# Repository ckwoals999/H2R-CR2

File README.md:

# H2R-CR2
Robot-Arduino-Cleaning Robot

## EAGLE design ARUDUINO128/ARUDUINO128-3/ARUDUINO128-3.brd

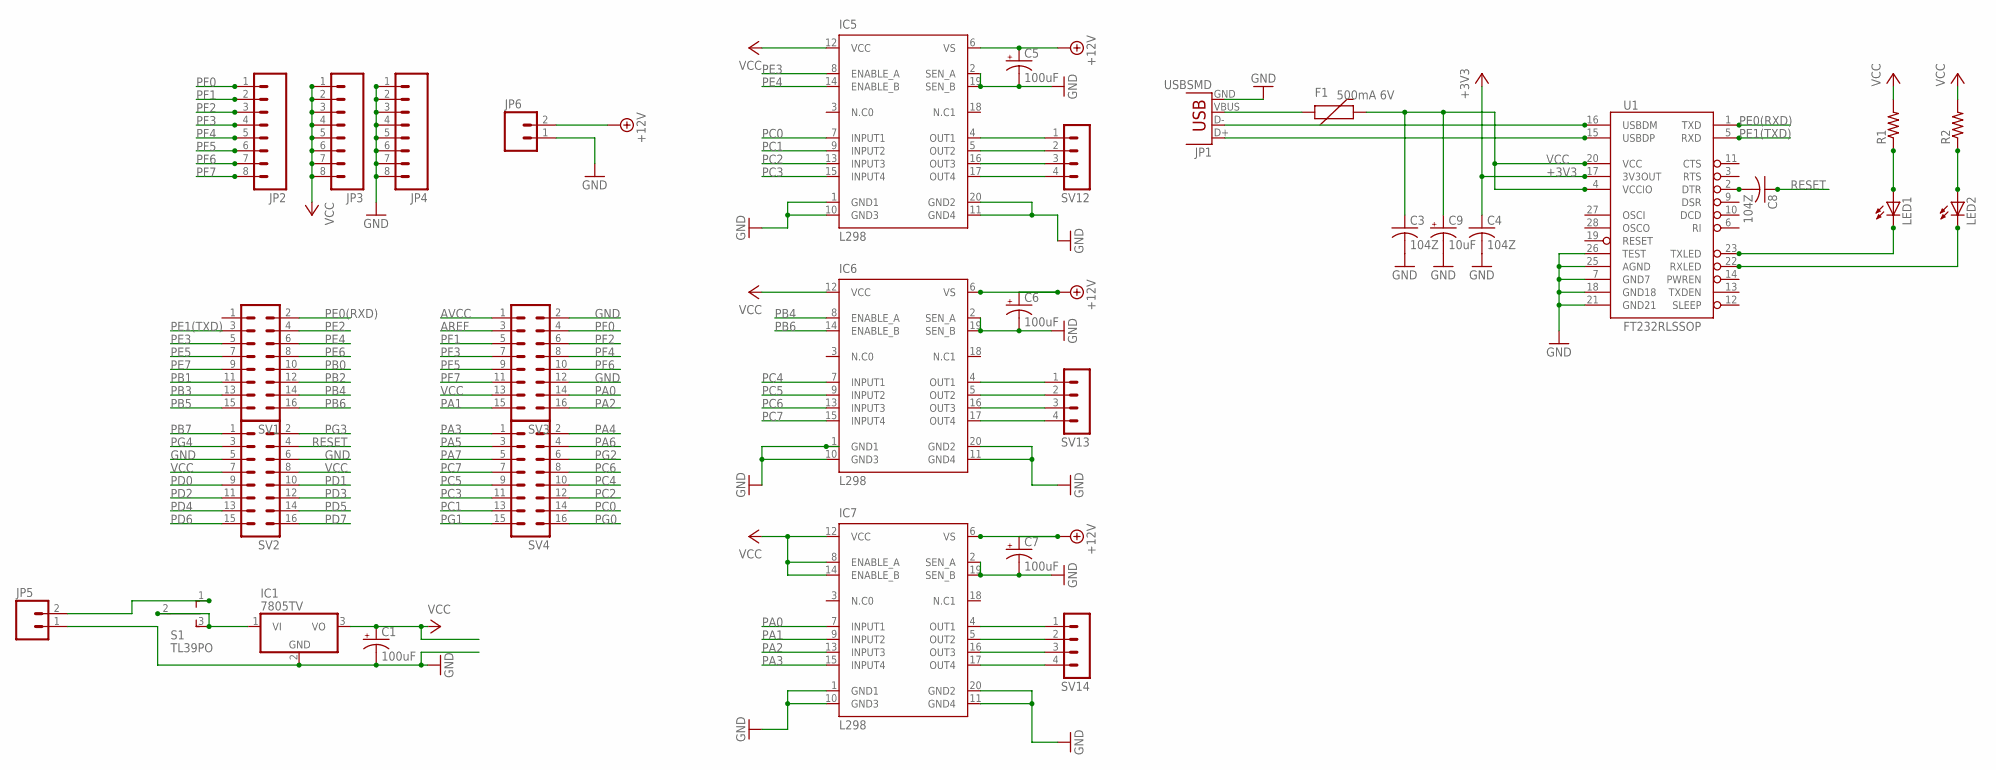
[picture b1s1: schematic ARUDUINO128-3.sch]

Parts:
C1, C5, C6, C7: 100uF; 153CLV-0807
C3, C4, C8: 104Z; C0603K
C9: 10uF; A/3216-18W
F1: 500mA 6V; PTC-1206
IC1: 7805TV; TO220V
IC5, IC6, IC7: L298; POWERSO-20
JP1: USBSMD; USB-MINIB
JP2, JP3, JP4: M08; 1X08_ROUND
JP5, JP6: M02PTH; 1X02
LED1, LED2: LEDCHIPLED_0603; CHIPLED_0603
R1, R2: R-US_M0805; M0805
S1: TL39PO; TL3XPO
SV1, SV2, SV3, SV4: MA08-2
SV12, SV13, SV14: MA04-1
U1: FT232RLSSOP; SSOP28DB

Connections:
+3V3: C4.1, U1.17 (3V3OUT)
+12V: C5.+, C6.+, C7.+, IC5.6 (VS), IC6.6 (VS), IC7.6 (VS), JP6.2
AREF: SV3.3
AVCC: SV3.1
GND: C1.-, C3.2, C4.2, C5.-, C6.-, C7.-, C9.-, IC1.2 (GND), IC5.1 (GND1), IC5.2 (SEN_A), IC5.10 (GND3), IC5.11 (GND4), IC5.19 (SEN_B), IC5.20 (GND2), IC6.1 (GND1), IC6.2 (SEN_A), IC6.10 (GND3), IC6.11 (GND4), IC6.19 (SEN_B), IC6.20 (GND2), IC7.1 (GND1), IC7.2 (SEN_A), IC7.10 (GND3), IC7.11 (GND4), IC7.19 (SEN_B), IC7.20 (GND2), JP1.GND, JP4.1, JP4.2, JP4.3, JP4.4, JP4.5, JP4.6, JP4.7, JP4.8, JP5.1, JP6.1, SV2.5, SV2.6, SV3.2, SV3.12, U1.7 (GND7), U1.18 (GND18), U1.21 (GND21), U1.25 (AGND), U1.26 (TEST)
unnamed: JP5.2, S1.1 (O)
unnamed: IC1.1 (VI), S1.2, S1.3 (S)
unnamed: F1.1, JP1.VBUS
unnamed: JP1.D-, U1.16 (USBDM)
unnamed: JP1.D+, U1.15 (USBDP)
unnamed: LED1.A, R1.1
unnamed: LED2.A, R2.1
unnamed: LED1.C, U1.23 (TXLED)
unnamed: LED2.C, U1.22 (RXLED)
unnamed: C8.2, U1.2 (DTR)
unnamed: IC5.4 (OUT1), SV12.1
unnamed: IC5.5 (OUT2), SV12.2
unnamed: IC5.16 (OUT3), SV12.3
unnamed: IC5.17 (OUT4), SV12.4
unnamed: IC6.4 (OUT1), SV13.1
unnamed: IC6.5 (OUT2), SV13.2
unnamed: IC6.16 (OUT3), SV13.3
unnamed: IC6.17 (OUT4), SV13.4
unnamed: IC7.4 (OUT1), SV14.1
unnamed: IC7.5 (OUT2), SV14.2
unnamed: IC7.16 (OUT3), SV14.3
unnamed: IC7.17 (OUT4), SV14.4
PA0: IC7.7 (INPUT1), SV3.14
PA1: IC7.9 (INPUT2), SV3.15
PA2: IC7.13 (INPUT3), SV3.16
PA3: IC7.15 (INPUT4), SV4.1
PA4: SV4.2
PA5: SV4.3
PA6: SV4.4
PA7: SV4.5
PB0: SV1.10
PB1: SV1.11
PB2: SV1.12
PB3: SV1.13
PB4: IC6.8 (ENABLE_A), SV1.14
PB5: SV1.15
PB6: IC6.14 (ENABLE_B), SV1.16
PB7: SV2.1
PC0: IC5.7 (INPUT1), SV4.14
PC1: IC5.9 (INPUT2), SV4.13
PC2: IC5.13 (INPUT3), SV4.12
PC3: IC5.15 (INPUT4), SV4.11
PC4: IC6.7 (INPUT1), SV4.10
PC5: IC6.9 (INPUT2), SV4.9
PC6: IC6.13 (INPUT3), SV4.8
PC7: IC6.15 (INPUT4), SV4.7
PD0: SV2.9
PD1: SV2.10
PD2: SV2.11
PD3: SV2.12
PD4: SV2.13
PD5: SV2.14
PD6: SV2.15
PD7: SV2.16
PE0(RXD): SV1.2, U1.1 (TXD)
PE1(TXD): SV1.3, U1.5 (RXD)
PE2: SV1.4
PE3: IC5.8 (ENABLE_A), SV1.5
PE4: IC5.14 (ENABLE_B), SV1.6
PE5: SV1.7
PE6: SV1.8
PE7: SV1.9
PF0: JP2.1, SV3.4
PF1: JP2.2, SV3.5
PF2: JP2.3, SV3.6
PF3: JP2.4, SV3.7
PF4: JP2.5, SV3.8
PF5: JP2.6, SV3.9
PF6: JP2.7, SV3.10
PF7: JP2.8, SV3.11
PG0: SV4.16
PG1: SV4.15
PG2: SV4.6
PG3: SV2.2
PG4: SV2.3
RESET: C8.1, SV2.4
VCC: C1.+, C3.1, C9.+, F1.2, IC1.3 (VO), IC5.12 (VCC), IC6.12 (VCC), IC7.8 (ENABLE_A), IC7.12 (VCC), IC7.14 (ENABLE_B), JP3.1, JP3.2, JP3.3, JP3.4, JP3.5, JP3.6, JP3.7, JP3.8, R1.2, R2.2, SV2.7, SV2.8, SV3.13, U1.4 (VCCIO), U1.20 (VCC)

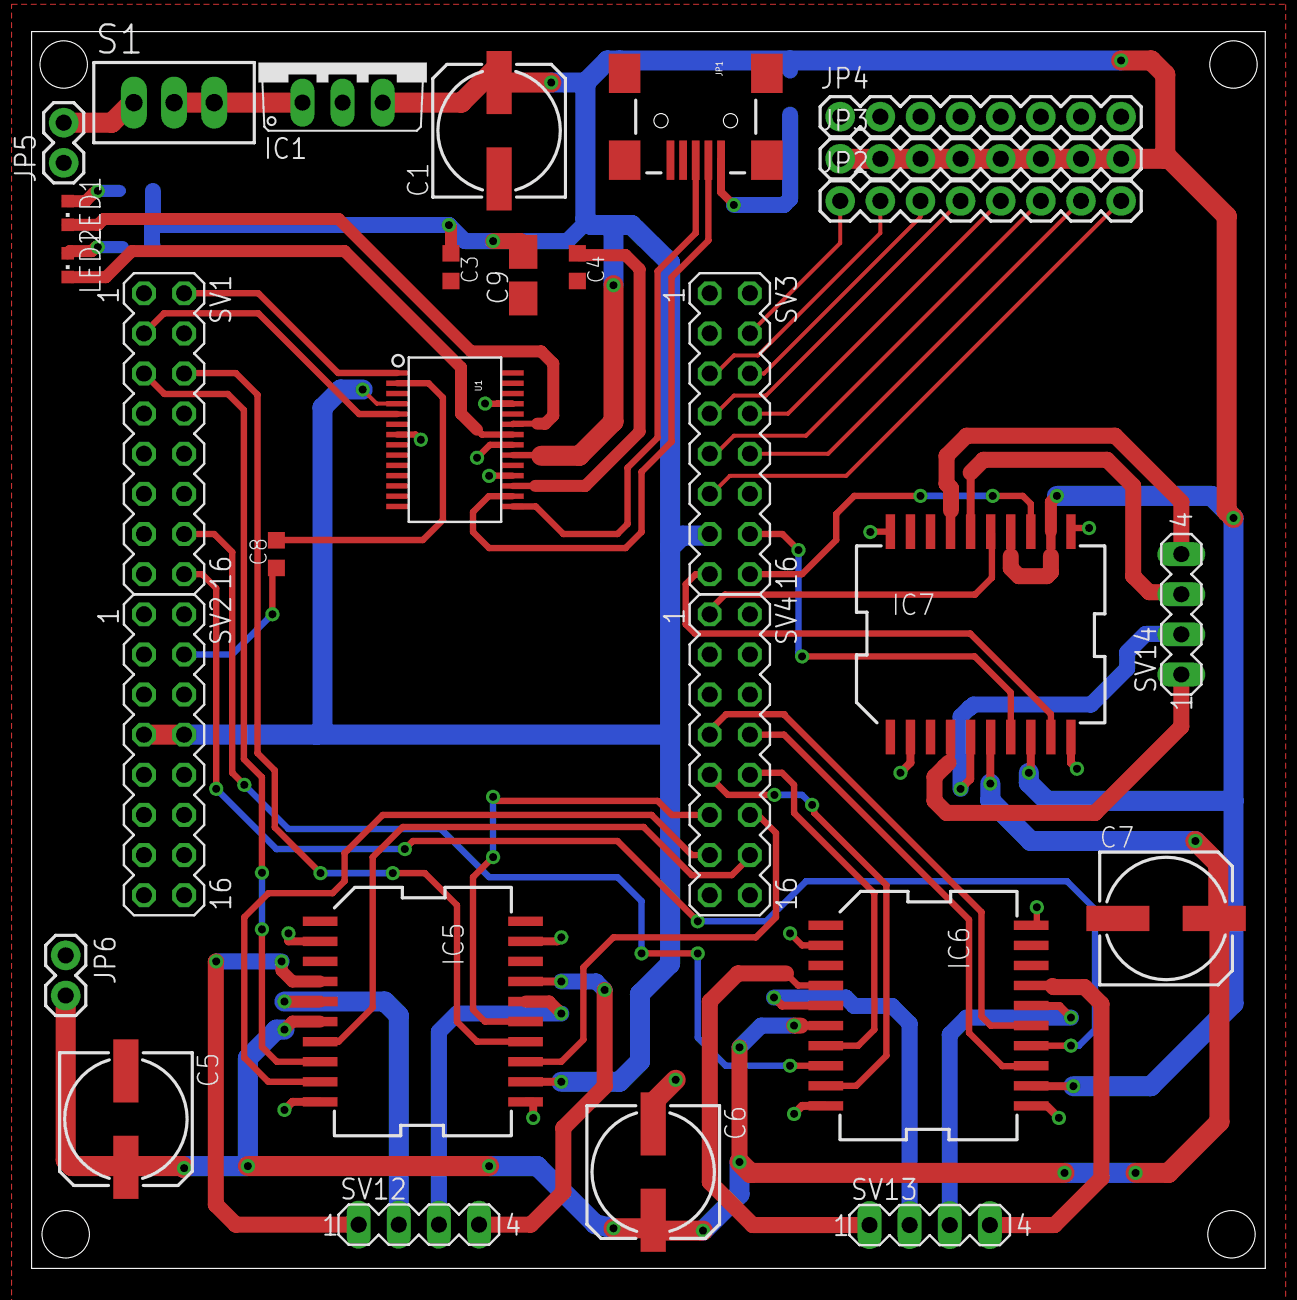
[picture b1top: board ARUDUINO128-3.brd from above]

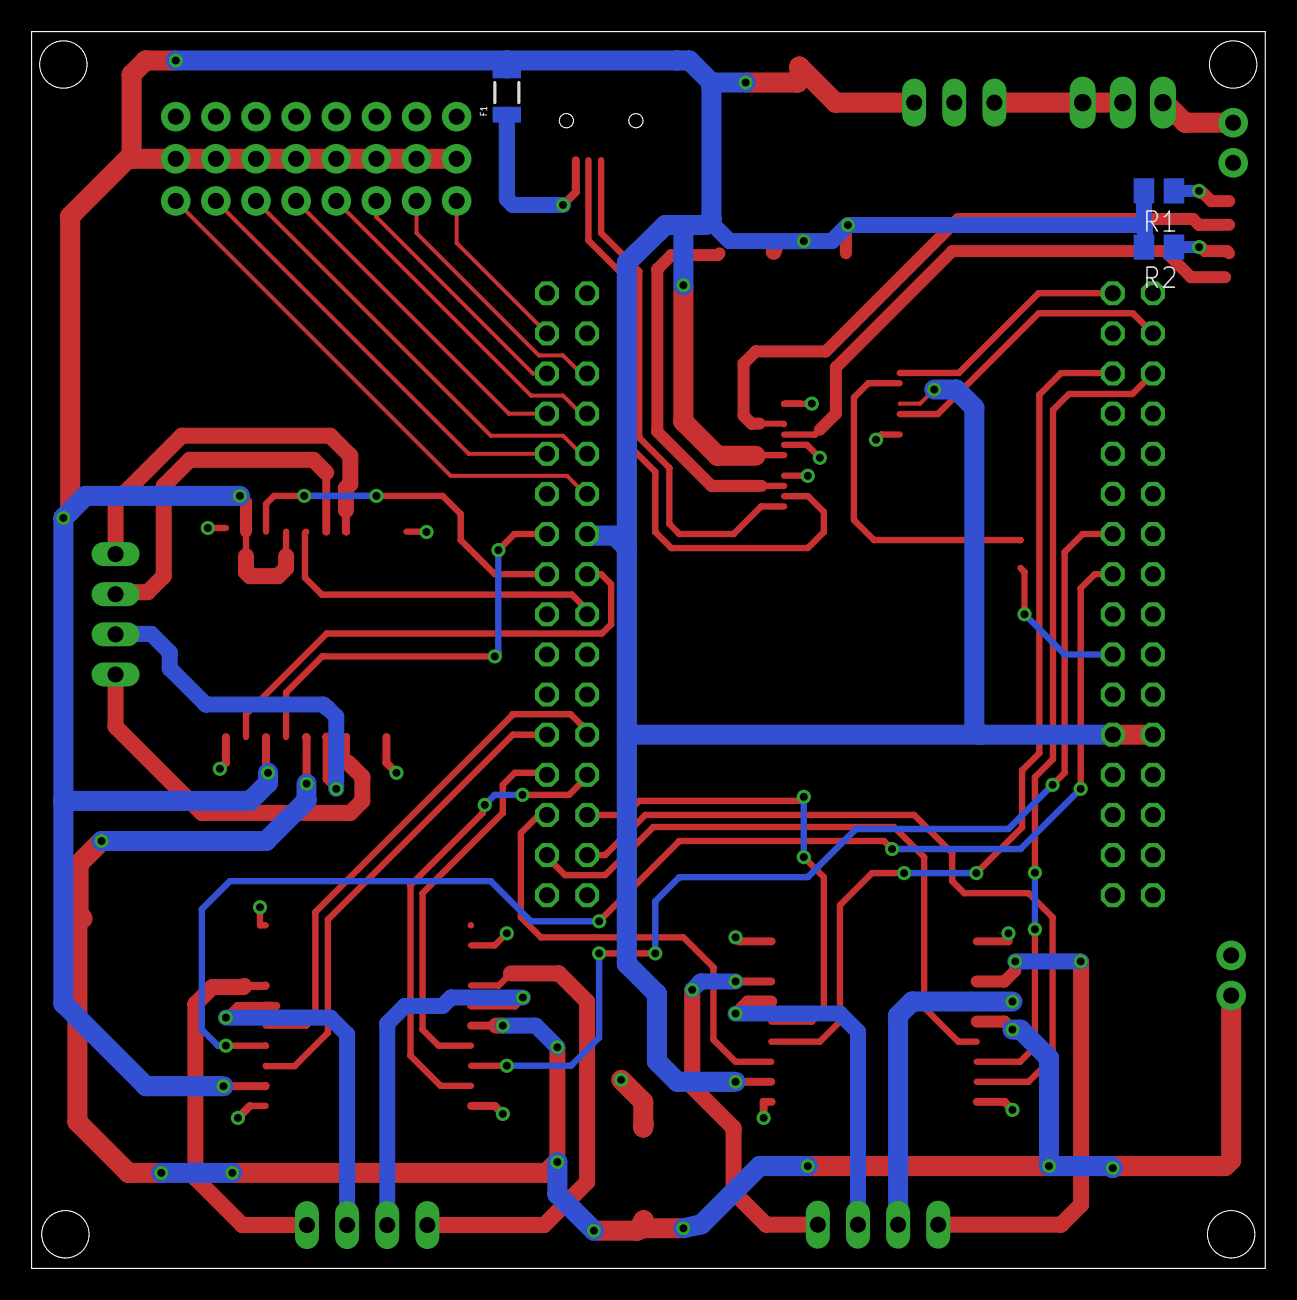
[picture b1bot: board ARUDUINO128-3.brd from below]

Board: 2 copper layers, 78.1 x 78.3 mm, 32 parts (3 on the bottom side), 53 nets.

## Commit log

2017-02-28 Create Circuit

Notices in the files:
parts and their libraries:
SparkFun-Connectors: Licensing: Creative Commons ShareAlike 4.0 International - https://creativecommons.org/licenses/by-sa/4.0
